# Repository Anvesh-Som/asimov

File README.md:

# asimov
Repository for autonomous mobile robot Asimov.

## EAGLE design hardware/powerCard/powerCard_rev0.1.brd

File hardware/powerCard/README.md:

## Power Card for Asimov

### Power Ports
|Port         |Functionality |Description                                               |
|-------------|:------------:|:---------------------------------------------------------|
|J1: B1       |INPUT         |Battery Power Port                                        |
|J2: CHG      |INPUT         |Charging Power Port                                       |
|J3: M1       |OUTPUT        |MAINS Power Port (enabled by MAIN Switch)                 |
|J4: MD       |OUTPUT        |Motor Driver Power Port (disabled by EMG Switch)          |
|J6: PWR      |OUTPUT        |Battery Power Port (direct)                               |

### Switches IO
|Port  |Functionality |Description |
|------|:------------:|:------------------------------------------|
|J5  :1|OUTPUT        |VCC (for MAIN Switch)                      |
|J5  :2|INPUT         |MAIN Switch (disabled if CHG Switch==ON)       |
|J5  :3|OUTPUT        |MAINS VCC (for EMG Switch)                 |
|||
|J10 :1|INPUT         |EMG Switch (disables port J4: MD)          |
|J10 :2|OUTPUT        |CHG VCC (for CHG Switch)                   |
|J10 :3|INPUT         |CHG Switch (disabled if CHG not plugged IN)|

### Indcators
|Port           |Signifies                            |Description |
|---------------|:------------------------------------|:-------------------------------------|
|J7 : MAINS IND |MAINS(J3: M1) enabled                |-|
|J8 : EMG IND   |Drive Emergency --> (J4 :MD disabled)|-|
|J9 : CHG IND   |Charging enabledn (CHG plugged IN)   |MAINS & MAINS IND disabled, J1,J2,&J6 active|

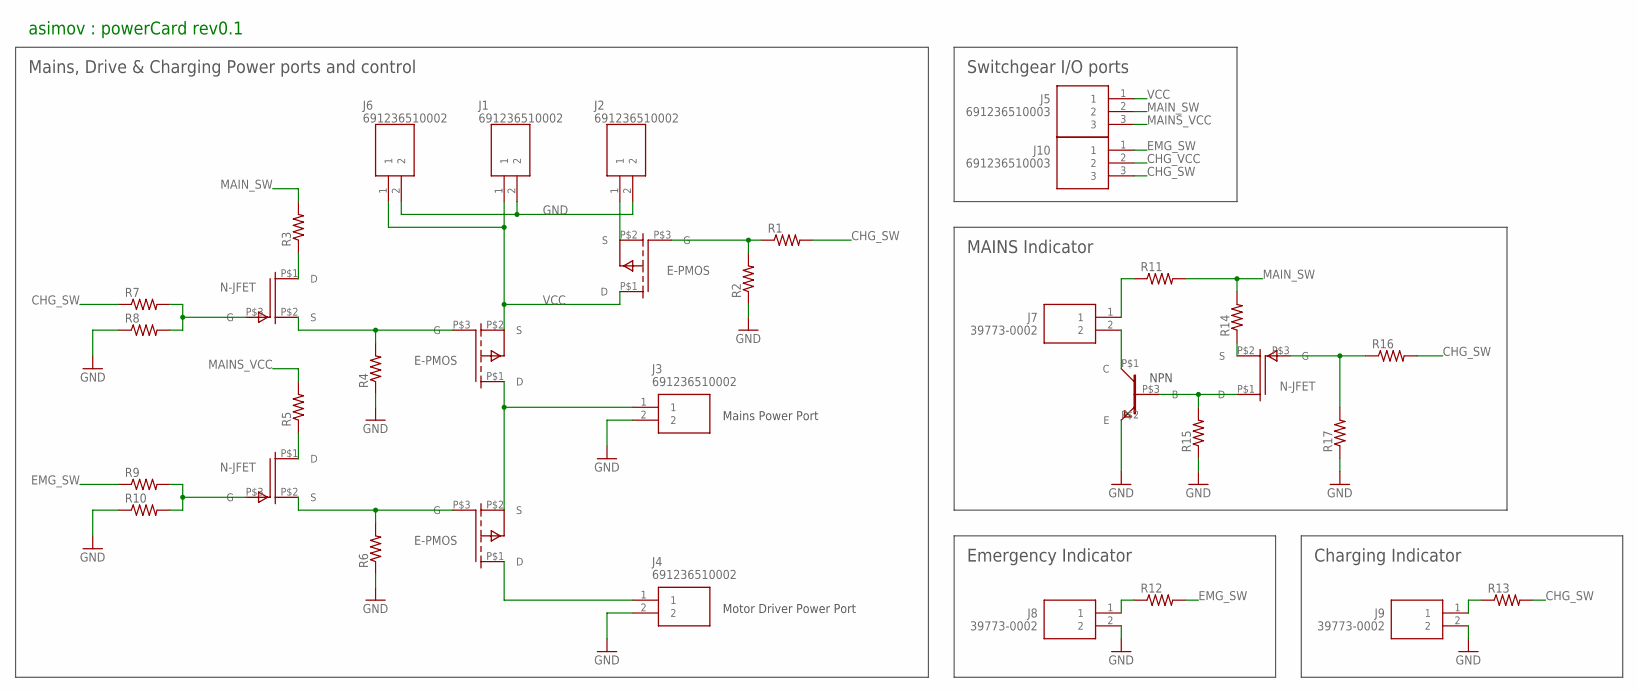
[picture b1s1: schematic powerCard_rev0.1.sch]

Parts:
J1, J2, J3, J4, J6: 691236510002; SHDR2W90P0X508_1X2_1076X1135X1
J5, J10: 691236510003; SHDR3W90P0X508_1X3_1524X1135X1
J7, J8, J9: 39773-0002; SHDR2W110P0X254_1X2_554X650X10
R1, R2, R3, R4, R5, R6, R7, R8, R9, R10, R11, R12, R13, R14, R15, R16, R17: R-US_0204/7; 0204/7
U$1, U$2, U$3: E-PMOSFET; TO-220
U$4, U$5, U$7: N-JFET; TO-92(3L)
U$6: NPN-BJT; TO-92

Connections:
CHG_GATE: R1.1, R2.2, U$1.P$3 (G)
CHG_SW: J10.3, R1.2, R7.1, R13.2, R16.2
CHG_VCC: J2.1, J10.2, U$1.P$2 (S)
EMG_GATE: R6.2, U$3.P$3 (G), U$5.P$2 (S)
EMG_SW: J10.1, R9.1, R12.2
GND: J1.2, J2.2, J3.2, J4.2, J6.2, J8.2, J9.2, R2.1, R4.1, R6.1, R8.1, R10.1, R15.1, R17.1, U$6.P$2 (E)
MAINS_GATE: R4.2, U$2.P$3 (G), U$4.P$2 (S)
MAINS_IND_BASE: R15.2, U$6.P$3 (B), U$7.P$1 (D)
MAINS_IND_GATE: R16.1, R17.2, U$7.P$3 (G)
MAINS_VCC: J3.1, J5.3, R5.2, U$2.P$1 (D), U$3.P$2 (S)
MAIN_SW: J5.2, R3.2, R11.2, R14.2
MD_VCC: J4.1, U$3.P$1 (D)
unnamed: R3.1, U$4.P$1 (D)
unnamed: R7.2, R8.2, U$4.P$3 (G)
unnamed: R9.2, R10.2, U$5.P$3 (G)
unnamed: J7.1, R11.1
unnamed: R5.1, U$5.P$1 (D)
unnamed: J8.1, R12.1
unnamed: J9.1, R13.1
unnamed: J7.2, U$6.P$1 (C)
unnamed: R14.1, U$7.P$2 (S)
VCC: J1.1, J5.1, J6.1, U$1.P$1 (D), U$2.P$2 (S)

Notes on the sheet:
Switchgear I/O ports
MAINS Indicator
Charging Indicator
Emergency Indicator
Mains, Drive & Charging Power ports and control
Mains Power Port
Motor Driver Power Port
asimov : powerCard rev0.1

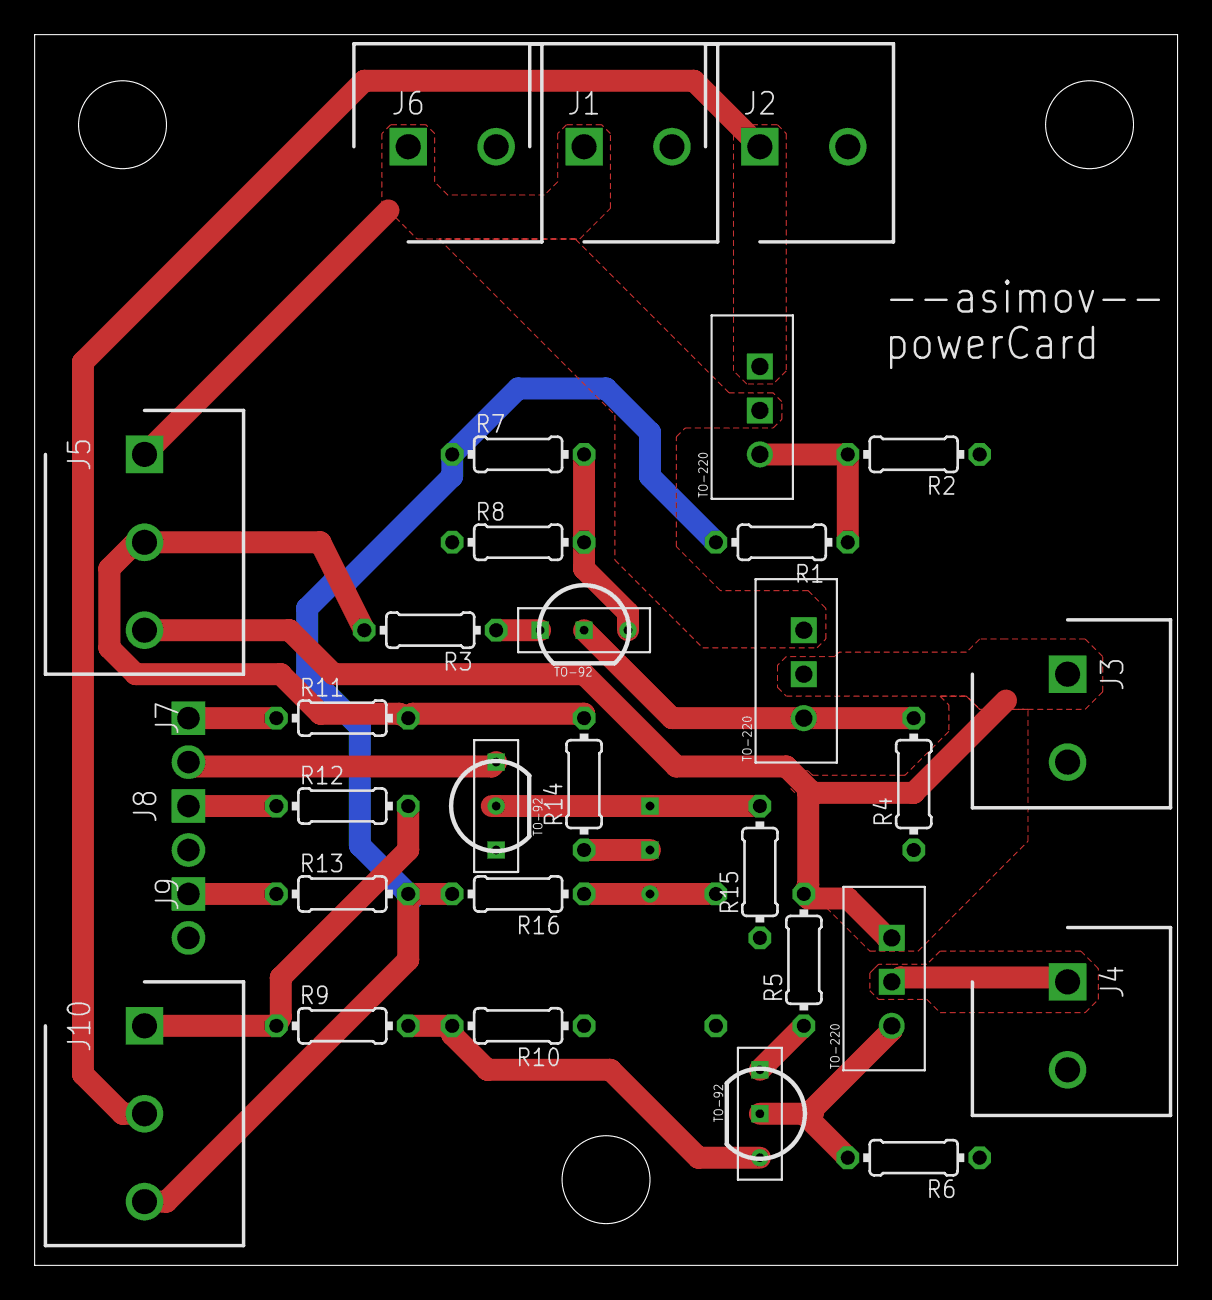
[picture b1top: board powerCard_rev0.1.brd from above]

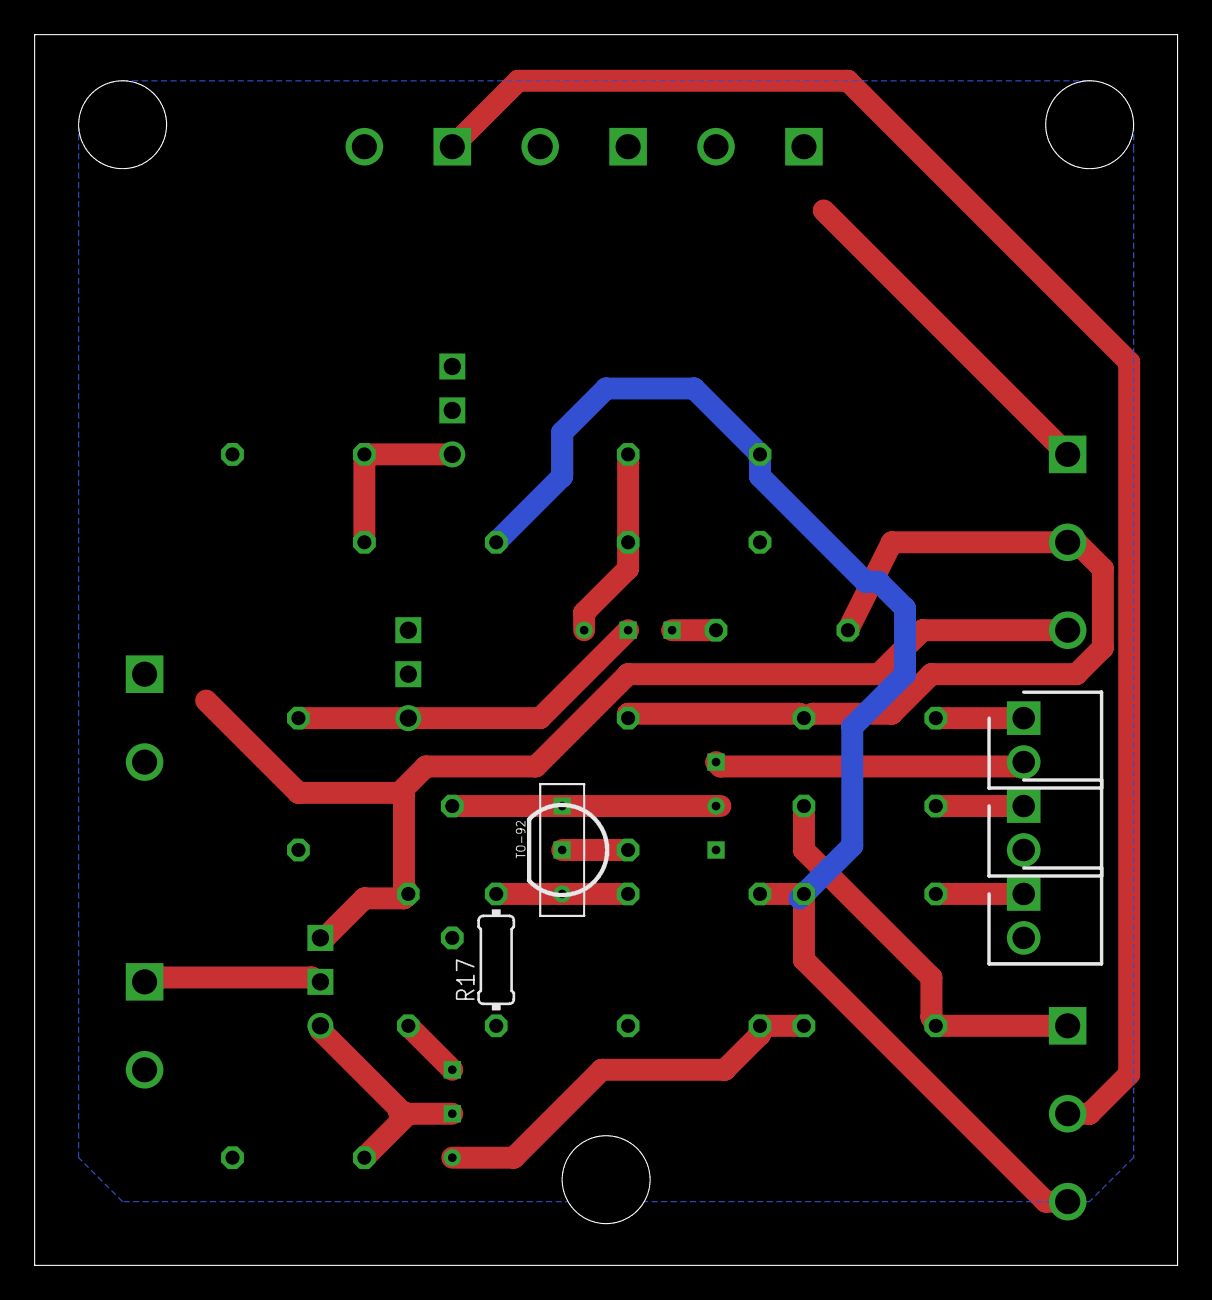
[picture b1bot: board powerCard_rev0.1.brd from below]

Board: 2 copper layers, 66.0 x 71.1 mm, 34 parts (5 on the bottom side), 22 nets.

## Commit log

2019-11-12 transistor symbols and footprints
2019-11-16 setup init.
2019-11-17 symbols and footprints updated to 0.1in.
2019-11-17 Update setup README
    Description of SD card image and how to get started.
2019-11-18 powerCard rev0.1 SCH & BRD
2019-11-18 README init for powerCard
2019-11-18 powerCard README update
2019-11-24 catkin_ws directory struc. & sketchbook
2020-02-03 setup readme update
2020-02-03 demo: catkin package, ros-topics
2020-02-05 added teleop package (py)
2020-02-09 roboclaw-ROS, arduino-sketch, mega2560
2020-03-01 error handling & PID values updated
2020-12-30 Added CAD files, Assembly and .step files
2021-01-02 Improved teleop to have different drive modes

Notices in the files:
parts and their libraries:
transistors: Licencse :
This work is licensed under the Creative Commons Attribution 4.0 International License.
To view a copy of this license, visit http://creativecommons.org/licenses/by/4.0
